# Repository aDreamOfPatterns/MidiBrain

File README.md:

# MidiBrain
Code base for the teensy 3.6 based eurorack module MidiBrain

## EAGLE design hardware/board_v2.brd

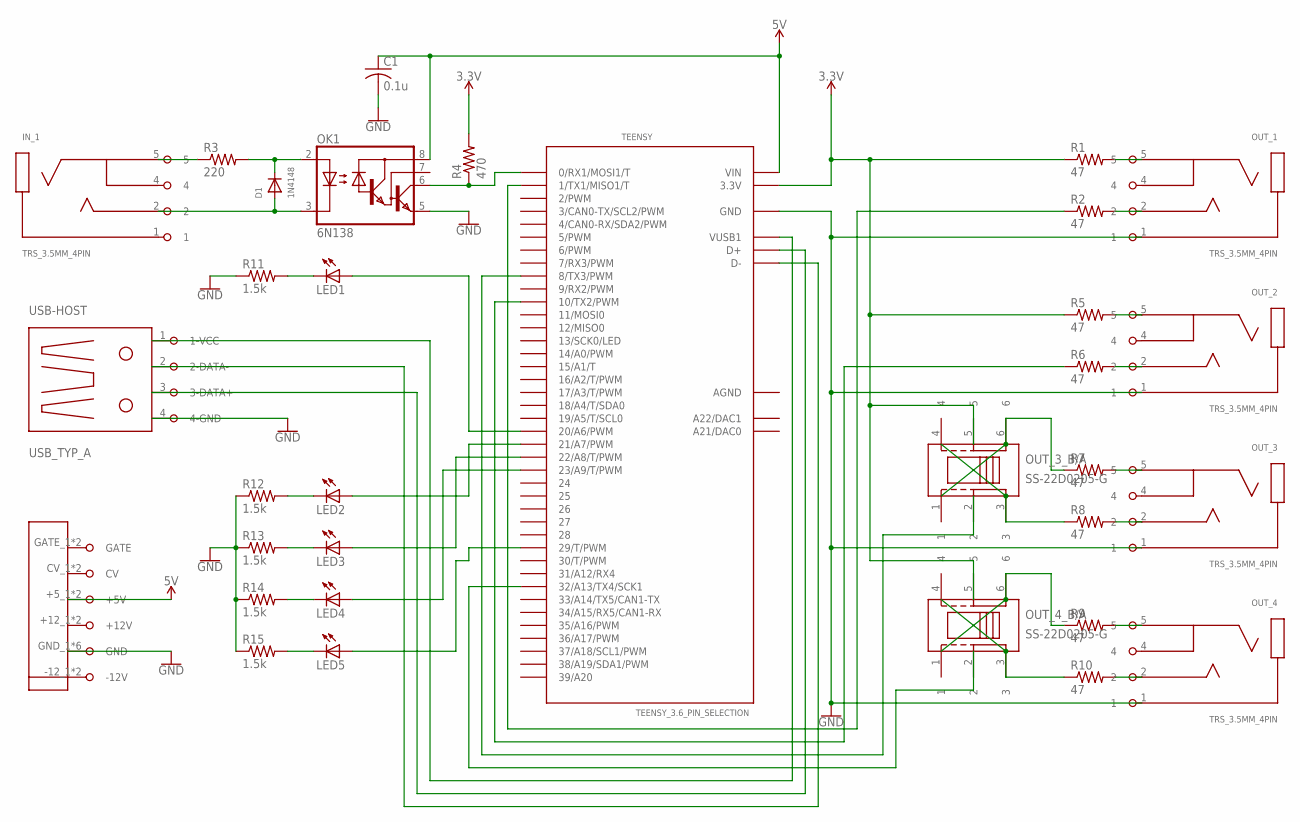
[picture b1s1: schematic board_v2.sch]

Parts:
C1: 0.1u; C0805
D1: 1N4148; DO-1N4148
IN_1: TRS_3.5MM_4PIN; FC681374V
LED1, LED2, LED3, LED4, LED5: LED3MM
OK1: 6N138; DIL08
OUT_1, OUT_2, OUT_3, OUT_4: TRS_3.5MM_4PIN; FC681374V
OUT_3_B/A, OUT_4_B/A: SS-22D0205-G
POWER: EURORACK_POWER_16
R1, R2, R5, R6, R7, R8, R9, R10: 47; R0805
R3: 220; R0805
R4: 470; R0805
R11, R12, R13, R14, R15: 1.5k; R0805
TEENSY: TEENSY_3.6_PIN_SELECTION
USB-HOST: USB_TYP_A; USB_HOST_VERTICAL

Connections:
3.3V: OUT_3_B/A.5, OUT_4_B/A.5, R1.1, R4.2, R5.1, TEENSY.3.3V, TEENSY.3.3V3 (3.3V)
5V: C1.1, OK1.8 (VCC), POWER.+5_1 (+5V), POWER.+5_2 (+5V), TEENSY.VIN
AGND: TEENSY.AGND
GND: C1.2, OK1.5 (GND), OUT_1.1, OUT_2.1, OUT_3.1, OUT_4.1, POWER.GND_1 (GND), POWER.GND_2 (GND), POWER.GND_3 (GND), POWER.GND_4 (GND), POWER.GND_5 (GND), POWER.GND_6 (GND), R11.1, R12.1, R13.1, R14.1, R15.1, TEENSY.GND, TEENSY.GND1 (GND), TEENSY.GND3 (GND), TEENSY.GND4 (GND), USB-HOST.4 (4-GND)
unnamed: OK1.6 (VO), R4.1, TEENSY.0 (0/RX1/MOSI1/T)
unnamed: D1.C, OK1.2 (A), R3.2
unnamed: D1.A, IN_1.2, OK1.3 (C)
unnamed: TEENSY.VUSB1, USB-HOST.1 (1-VCC)
unnamed: R2.1, TEENSY.1 (1/TX1/MISO1/T)
unnamed: OUT_1.2, R2.2
unnamed: OUT_1.5, R1.2
unnamed: OUT_3.2, R8.2
unnamed: IN_1.5, R3.1
unnamed: OUT_2.2, R6.2
unnamed: OUT_2.5, R5.2
unnamed: OUT_3.5, R7.2
unnamed: OUT_4.2, R10.2
unnamed: OUT_4.5, R9.2
unnamed: TEENSY.D+, USB-HOST.3 (3-DATA+)
unnamed: TEENSY.D-, USB-HOST.2 (2-DATA-)
unnamed: LED1.K (C), R11.2
unnamed: R6.1, TEENSY.10 (10/TX2/PWM)
unnamed: OUT_3_B/A.2, TEENSY.8 (8/TX3/PWM)
unnamed: OUT_4_B/A.2, TEENSY.32/A13 (32/A13/TX4/SCK1)
unnamed: OUT_4_B/A.3, OUT_4_B/A.4, R10.1
unnamed: LED1.A, TEENSY.20/A6 (20/A6/PWM)
unnamed: OUT_4_B/A.1, OUT_4_B/A.6, R9.1
unnamed: OUT_3_B/A.1, OUT_3_B/A.6, R7.1
unnamed: OUT_3_B/A.3, OUT_3_B/A.4, R8.1
unnamed: LED5.K (C), R15.2
unnamed: LED2.K (C), R12.2
unnamed: LED3.K (C), R13.2
unnamed: LED4.K (C), R14.2
unnamed: LED2.A, TEENSY.21/A7 (21/A7/PWM)
unnamed: LED3.A, TEENSY.22/A8 (22/A8/T/PWM)
unnamed: LED4.A, TEENSY.23/A9 (23/A9/T/PWM)
unnamed: LED5.A, TEENSY.29 (29/T/PWM)

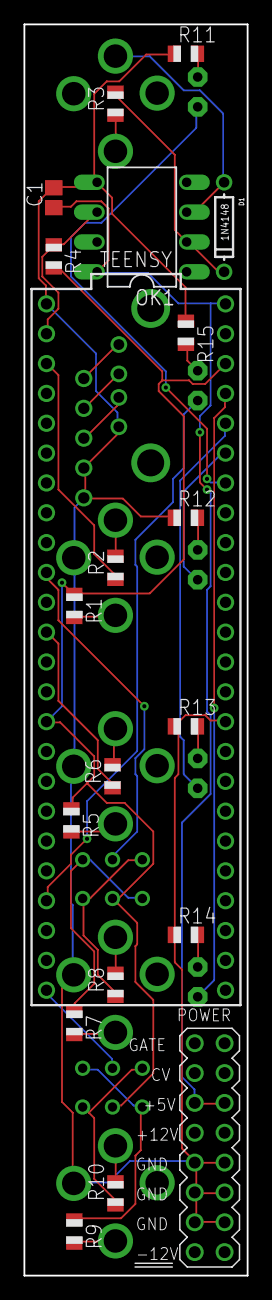
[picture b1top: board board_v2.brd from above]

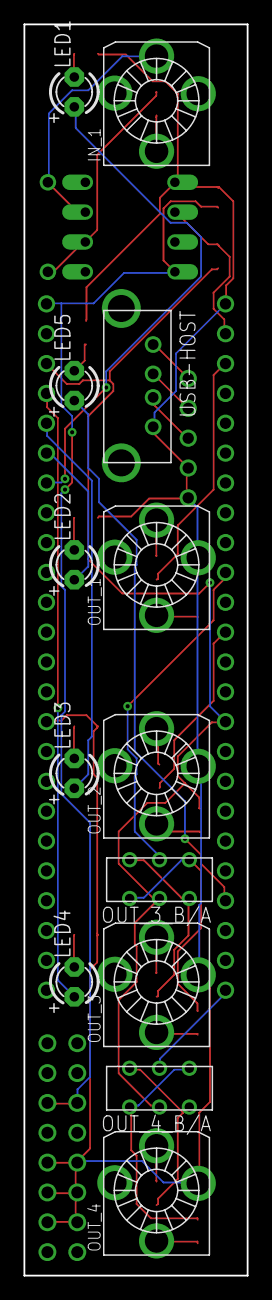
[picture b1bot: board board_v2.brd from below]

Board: 2 copper layers, 19.0 x 106.5 mm, 33 parts (13 on the bottom side), 36 nets.

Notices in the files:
parts and their libraries:
SparkFun-PowerSymbols: Licensing: Creative Commons ShareAlike 4.0 International - https://creativecommons.org/licenses/by-sa/4.0
